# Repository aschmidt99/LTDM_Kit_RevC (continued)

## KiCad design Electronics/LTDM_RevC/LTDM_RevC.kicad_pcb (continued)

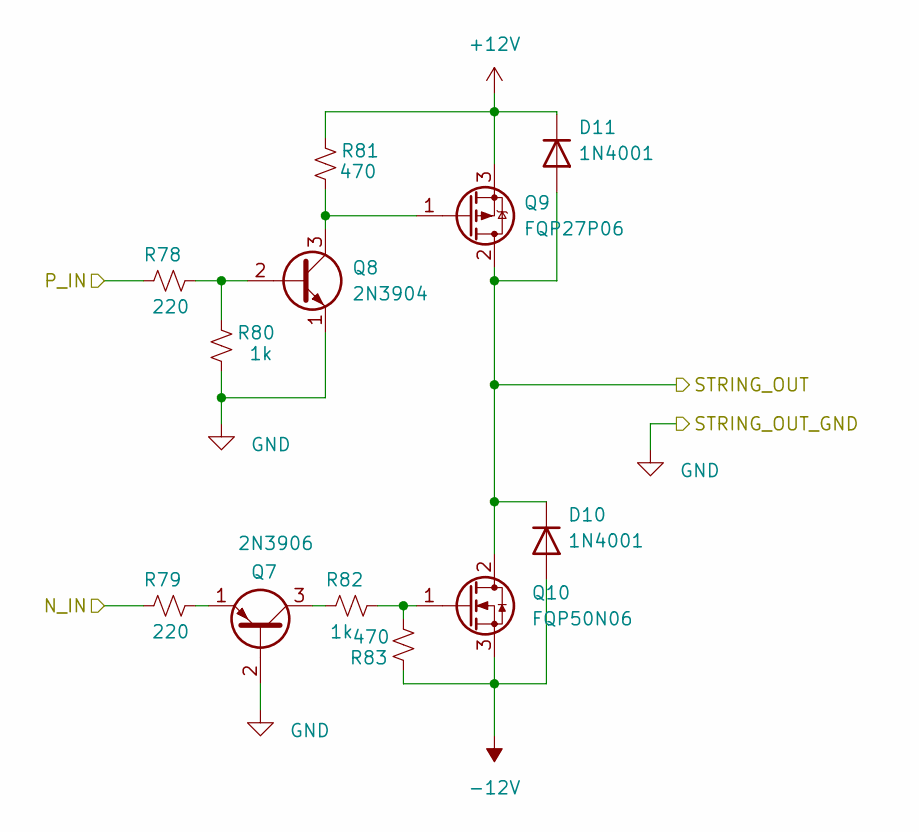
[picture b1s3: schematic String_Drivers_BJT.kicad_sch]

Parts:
D10, D11: 1N4001; D_DO-34_SOD68_P7.62mm_Horizontal
Q7: 2N3906; TO-92_Inline
Q8: 2N3904; TO-92_Inline
Q9: FQP27P06; TO-220-3_Vertical
Q10: FQP50N06; TO-220-3_Vertical; LCSC C2710
R78, R79: 220; R_0603_1608Metric
R80, R82: 1k; R_0603_1608Metric
R81, R83: 470; R_0603_1608Metric

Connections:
unnamed: D10.1 (K), D11.2 (A), Q9.2 (D), Q10.2 (D)
unnamed: D10.2 (A), Q10.3 (S), R83.2
unnamed: D11.1 (K), Q9.3 (S), R81.2
unnamed: Q7.1 (E), R79.2
unnamed: Q7.2 (B), Q8.1 (E), R80.1
unnamed: Q7.3 (C), R82.1
unnamed: Q8.2 (B), R78.2, R80.2
unnamed: Q8.3 (C), Q9.1 (G), R81.1
unnamed: Q10.1 (G), R82.2, R83.1

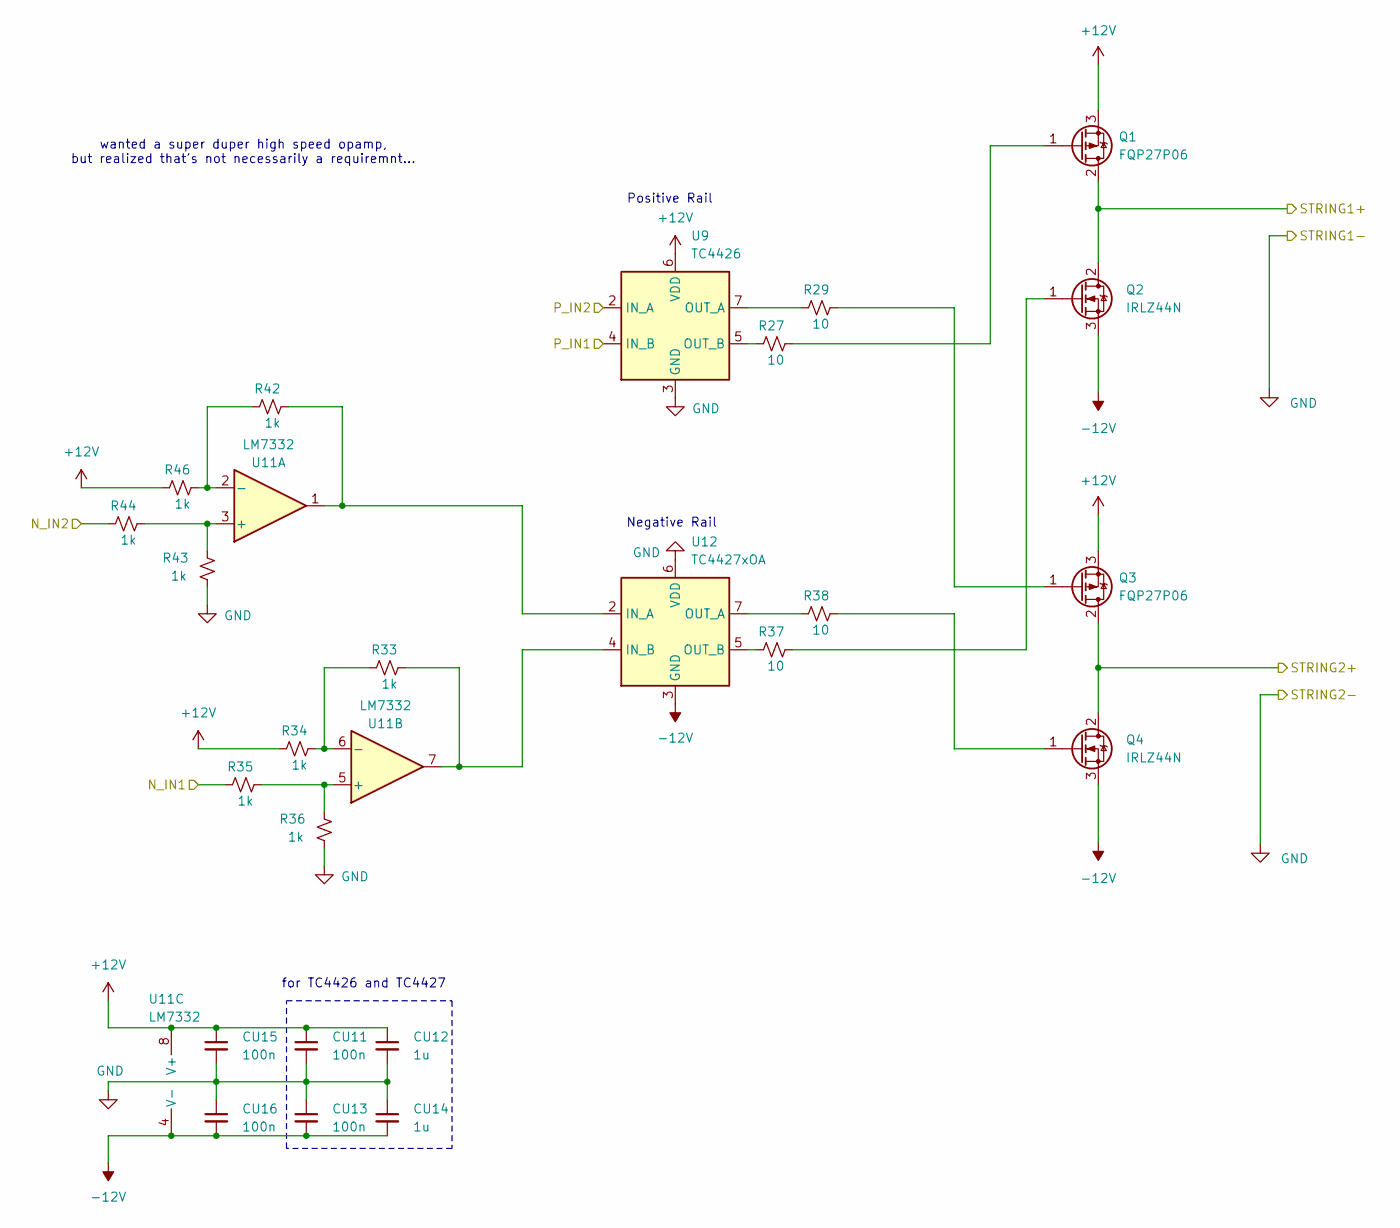
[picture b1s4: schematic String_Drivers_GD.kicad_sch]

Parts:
CU11, CU13, CU15, CU16: 100n; C_0603_1608Metric
CU12, CU14: 1u; C_0805_2012Metric; LCSC C24123
Q1, Q3: FQP27P06; TO-220-3_Vertical; LCSC C7503194
Q2, Q4: IRLZ44N; TO-220-3_Vertical; LCSC C22367197
R27, R29, R37, R38: 10; R_0603_1608Metric
R33, R34, R35, R36, R42, R43, R44, R46: 1k; R_0603_1608Metric
U9: TC4426; SOIC-8_3.9x4.9mm_P1.27mm; LCSC C148047
U11: LM7332; SOP-8_3.76x4.96mm_P1.27mm; LCSC C97826
U12: TC4427xOA; SOIC-8_3.9x4.9mm_P1.27mm; LCSC C636893

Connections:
+12V: CU11.1, CU12.1, CU15.1, Q1.3 (S), Q3.3 (S), R34.1, R46.1, U9.6 (VDD), U11.8 (V+); also elsewhere on the board
-12V: CU13.2, CU14.2, CU16.2, Q2.3 (S), Q4.3 (S), U11.4 (V-), U12.3 (GND); also elsewhere on the board
/String_Drivers_GD1/N_IN1: R35.1; also elsewhere on the board
/String_Drivers_GD1/N_IN2: R44.1; also elsewhere on the board
/String_Drivers_GD1/P_IN1: U9.4 (IN_B); also elsewhere on the board
/String_Drivers_GD1/P_IN2: U9.2 (IN_A); also elsewhere on the board
GND: CU11.2, CU12.2, CU13.1, CU14.1, CU15.2, CU16.1, R36.1, R43.1, U9.3 (GND), U12.6 (VDD); also elsewhere on the board
unnamed: Q1.1 (G), R27.2
unnamed: Q2.1 (G), R37.2
unnamed: Q3.1 (G), R29.2
unnamed: Q4.1 (G), R38.2
unnamed: R29.1, U9.7 (OUT_A)
unnamed: R27.1, U9.5 (OUT_B)
unnamed: R43.2, R44.2, U11.3 (+)
unnamed: R42.1, R46.2, U11.2 (-)
unnamed: R35.2, R36.2, U11.5 (+)
unnamed: R33.1, R34.2, U11.6 (-)
unnamed: R42.2, U11.1, U12.2 (IN_A)
unnamed: R33.2, U11.7, U12.4 (IN_B)
unnamed: R38.1, U12.7 (OUT_A)
unnamed: R37.1, U12.5 (OUT_B)
pre_resistor1: Q1.2 (D), Q2.2 (D); also elsewhere on the board
pre_resistor2: Q3.2 (D), Q4.2 (D); also elsewhere on the board

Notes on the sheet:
wanted a super duper high speed opamp, but realized that's not necessarily a requiremnt...
Negative Rail
Positive Rail
for TC4426 and TC4427

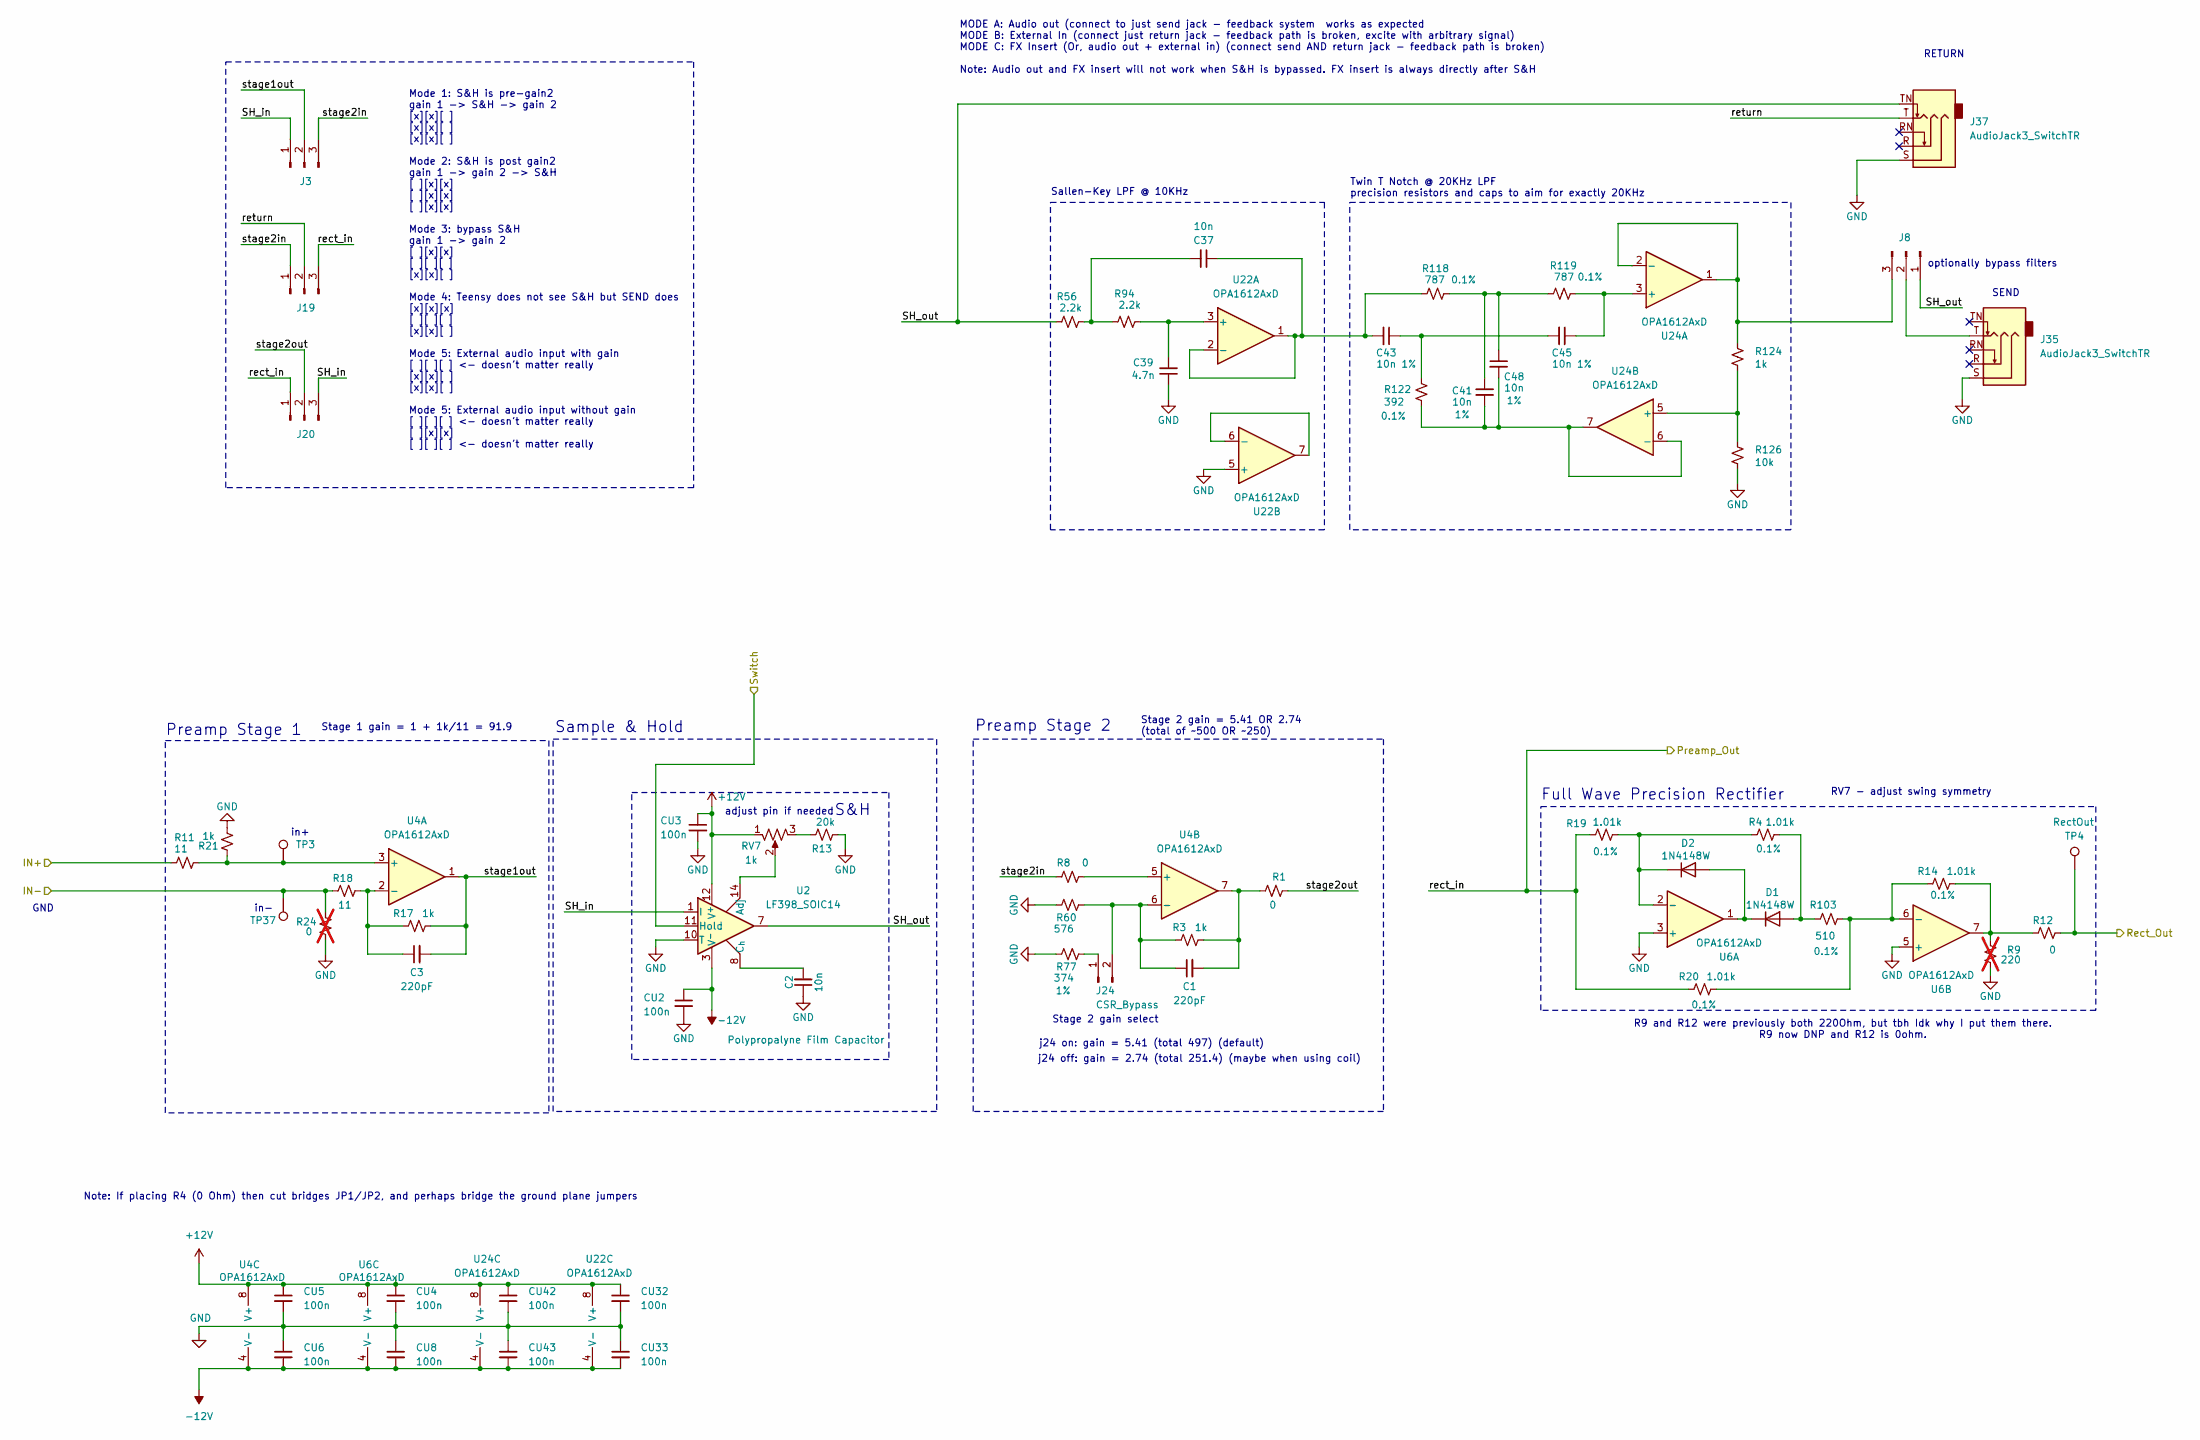
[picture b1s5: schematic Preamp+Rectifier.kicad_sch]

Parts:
C1, C3: 220pF; C_0603_1608Metric
C2: 10n; C_Rect_L11.0mm_W5.1mm_P10.00mm_MKT; LCSC C183540
C37: 10n; C_0603_1608Metric
C39: 4.7n; C_0603_1608Metric
C41, C43, C45, C48: 10n; C_0603_1608Metric; LCSC C3836718
CU2, CU3, CU4, CU5, CU6, CU8, CU32, CU33, CU42, CU43: 100n; C_0603_1608Metric
D1, D2: 1N4148W; D_SOD-123; LCSC C5345962
J3, J8, J19, J20: Conn_01x03_Male; PinHeader_1x03_P2.54mm_Vertical; LCSC C2914353
J24: CSR_Bypass; PinHeader_1x02_P2.54mm_Vertical; LCSC C124375
J35, J37: AudioJack3_SwitchTR; Jack_3.5mm_CUI_SJ1-3535NG_Horizontal; LCSC C4991610
R1, R8, R12: 0; R_0603_1608Metric
R3, R17, R21, R124: 1k; R_0603_1608Metric
R4, R14, R19, R20: 1.01k; R_0603_1608Metric; LCSC C861188
R9: 220; R_0603_1608Metric; not fitted
R11, R18: 11; R_0603_1608Metric; LCSC C861645
R13: 20k; R_0603_1608Metric
R24: 0; R_0603_1608Metric; not fitted
R56, R94: 2.2k; R_0603_1608Metric
R60: 576; R_0603_1608Metric; LCSC C705869
R77: 374; R_0603_1608Metric; LCSC C666871
R103: 510; R_0603_1608Metric; LCSC C309660
R118, R119: 787; R_0402_1005Metric; LCSC C728564
R122: 392; R_0603_1608Metric; LCSC C861870
R126: 10k; R_0603_1608Metric
RV7: 1k; Potentiometer_Bourns_3314G_Vertical; LCSC C780221
TP3, TP37: TestPoint; TestPoint_THTPad_D2.0mm_Drill1.0mm
TP4: RectOut; TestPoint_THTPad_D2.0mm_Drill1.0mm; LCSC C238122
U2: LF398_SOIC14; SOIC-14_3.9x8.7mm_P1.27mm; LCSC C2864267
U4, U6, U22, U24: OPA1612AxD; SOP-8_3.76x4.96mm_P1.27mm; LCSC C94590

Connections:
+12V: CU3.1, CU4.1, CU5.1, CU32.1, CU42.1, RV7.1, U2.12 (V^{+}), U4.8 (V+), U6.8 (V+), U22.8 (V+), U24.8 (V+); also elsewhere on the board
-12V: CU2.1, CU6.2, CU8.2, CU33.2, CU43.2, U2.3 (V^{-}), U4.4 (V-), U6.4 (V-), U22.4 (V-), U24.4 (V-); also elsewhere on the board
/Preamp+Rectifier1/IN+: R11.2; also elsewhere on the board
/Preamp+Rectifier1/IN-: R18.1, R24.2, TP37.1 (1_1); also elsewhere on the board
/Preamp+Rectifier1/Rect_Out: R12.2, TP4.1 (1_1); also elsewhere on the board
/Preamp+Rectifier1/SH_in: J3.1, J20.3, U2.1 (I)
/Preamp+Rectifier1/SH_out: J8.1, J37.TN, R56.2, U2.7
/Preamp+Rectifier1/rect_in: J19.3, J20.1, R19.1, R20.1; also elsewhere on the board
/Preamp+Rectifier1/return: J19.2, J37.T
/Preamp+Rectifier1/stage1out: C3.2, J3.2, R17.2, U4.1
/Preamp+Rectifier1/stage2in: J3.3, J19.1, R8.2
/Preamp+Rectifier1/stage2out: J20.2, R1.2
GND: C2.1, C39.1, CU2.2, CU3.2, CU4.2, CU5.2, CU6.1, CU8.1, CU32.2, CU33.1, CU42.2, CU43.1, J35.S, J37.S, R9.1, R13.2, R21.1, R24.1, R60.1, R77.1, R126.2, U2.10 (T), U6.3 (+), U6.5 (+), U22.5 (+); also elsewhere on the board
unnamed: C1.2, R1.1, R3.2, U4.7
unnamed: C37.2, R56.1, R94.2
unnamed: C41.1, C48.1, R118.1, R119.2
unnamed: C43.1, C45.2, R122.1
unnamed: D1.2 (A), R4.2, R103.1
unnamed: D1.1 (K), D2.2 (A), U6.1
unnamed: D2.1 (K), R4.1, R19.2, U6.2 (-)
unnamed: J8.2, J35.T
unnamed: J8.3, R124.1, U24.1, U24.2 (-)
unnamed: J24.1, R77.2
unnamed: C1.1, J24.2, R3.1, R60.2, U4.6 (-)
unnamed: R9.2, R12.1, R14.2, U6.7
unnamed: R13.1, RV7.3
unnamed: RV7.2, U2.14 (Adj)
unnamed: C2.2, U2.8 (C_{h})
unnamed: R11.1, R21.2, TP3.1 (1_1), U4.3 (+)
unnamed: C3.1, R17.1, R18.2, U4.2 (-)
unnamed: R8.1, U4.5 (+)
unnamed: R14.1, R20.2, R103.2, U6.6 (-)
unnamed: C39.2, R94.1, U22.3 (+)
unnamed: C37.1, C43.2, R118.2, U22.1, U22.2 (-)
unnamed: U22.6 (-), U22.7
unnamed: C45.1, R119.1, U24.3 (+)
unnamed: R124.2, R126.1, U24.5 (+)
unnamed: C41.2, C48.2, R122.2, U24.6 (-), U24.7
sample: U2.11 (Hold); also elsewhere on the board

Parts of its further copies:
C30, C34: 220pF; C_0603_1608Metric
C33: 10n; C_Rect_L11.0mm_W5.1mm_P10.00mm_MKT; LCSC C183540
C38: 10n; C_0603_1608Metric
C40: 4.7n; C_0603_1608Metric
C42, C44, C46, C49: 10n; C_0603_1608Metric; LCSC C3836718
CU18, CU19, CU21, CU23, CU24, CU25, CU39, CU40, CU44, CU45: 100n; C_0603_1608Metric
D7, D9: 1N4148W; D_SOD-123; LCSC C5345962
J10, J21, J27, J30: Conn_01x03_Male; PinHeader_1x03_P2.54mm_Vertical; LCSC C2914353
J28: CSR_Bypass; PinHeader_1x02_P2.54mm_Vertical; LCSC C124375
J36, J38: AudioJack3_SwitchTR; Jack_3.5mm_CUI_SJ1-3535NG_Horizontal; LCSC C4991610
R49, R59, R63: 0; R_0603_1608Metric
R51, R70, R73, R125: 1k; R_0603_1608Metric
R52, R65, R68, R69: 1.01k; R_0603_1608Metric; LCSC C861188
R57: 220; R_0603_1608Metric; not fitted
R58, R71: 11; R_0603_1608Metric; LCSC C861645
R62: 20k; R_0603_1608Metric
R64: 374; R_0603_1608Metric; LCSC C666871
R72, R117: 2.2k; R_0603_1608Metric
R75: 0; R_0603_1608Metric; not fitted
R76: 576; R_0603_1608Metric; LCSC C705869
R104: 510; R_0603_1608Metric; LCSC C309660
R120, R121: 787; R_0402_1005Metric; LCSC C728564
R123: 392; R_0603_1608Metric; LCSC C861870
R127: 10k; R_0603_1608Metric
RV10: 1k; Potentiometer_Bourns_3314G_Vertical; LCSC C780221
TP24: RectOut; TestPoint_THTPad_D2.0mm_Drill1.0mm; LCSC C238122
TP25, TP38: TestPoint; TestPoint_THTPad_D2.0mm_Drill1.0mm
U13, U14, U23, U25: OPA1612AxD; SOP-8_3.76x4.96mm_P1.27mm; LCSC C94590
U16: LF398_SOIC14; SOIC-14_3.9x8.7mm_P1.27mm; LCSC C2864267

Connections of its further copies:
+12V: CU18.1, CU19.1, CU23.1, CU39.1, CU44.1, RV10.1, U13.8 (V+), U14.8 (V+), U16.12 (V^{+}), U23.8 (V+), U25.8 (V+); also elsewhere on the board
-12V: CU21.2, CU24.1, CU25.2, CU40.2, CU45.2, U13.4 (V-), U14.4 (V-), U16.3 (V^{-}), U23.4 (V-), U25.4 (V-); also elsewhere on the board
/Preamp+Rectifier2/IN+: R58.2; also elsewhere on the board
/Preamp+Rectifier2/IN-: R71.1, R75.2, TP38.1 (1_1); also elsewhere on the board
/Preamp+Rectifier2/Rect_Out: R63.2, TP24.1 (1_1); also elsewhere on the board
/Preamp+Rectifier2/SH_in: J21.1, J30.3, U16.1 (I)
/Preamp+Rectifier2/SH_out: J10.1, J38.TN, R72.2, U16.7
/Preamp+Rectifier2/rect_in: J27.3, J30.1, R68.1, R69.1; also elsewhere on the board
/Preamp+Rectifier2/return: J27.2, J38.T
/Preamp+Rectifier2/stage1out: C34.2, J21.2, R70.2, U13.1
/Preamp+Rectifier2/stage2in: J21.3, J27.1, R59.2
/Preamp+Rectifier2/stage2out: J30.2, R49.2
GND: C33.1, C40.1, CU18.2, CU19.2, CU21.1, CU23.2, CU24.2, CU25.1, CU39.2, CU40.1, CU44.2, CU45.1, J36.S, J38.S, R57.1, R62.2, R64.1, R73.1, R75.1, R76.1, R127.2, U14.3 (+), U14.5 (+), U16.10 (T), U23.5 (+); also elsewhere on the board
unnamed: C30.2, R49.1, R51.2, U13.7
unnamed: C38.2, R72.1, R117.2
unnamed: C42.1, C49.1, R120.1, R121.2
unnamed: C44.1, C46.2, R123.1
unnamed: D7.2 (A), R52.2, R104.1
unnamed: D7.1 (K), D9.2 (A), U14.1
unnamed: D9.1 (K), R52.1, R68.2, U14.2 (-)
unnamed: J10.2, J36.T
unnamed: J10.3, R125.1, U25.1, U25.2 (-)
unnamed: J28.1, R64.2
unnamed: C30.1, J28.2, R51.1, R76.2, U13.6 (-)
unnamed: R57.2, R63.1, R65.2, U14.7
unnamed: R62.1, RV10.3
unnamed: R58.1, R73.2, TP25.1 (1_1), U13.3 (+)
unnamed: C34.1, R70.1, R71.2, U13.2 (-)
unnamed: R59.1, U13.5 (+)
unnamed: R65.1, R69.2, R104.2, U14.6 (-)
unnamed: RV10.2, U16.14 (Adj)
unnamed: C33.2, U16.8 (C_{h})
unnamed: C40.2, R117.1, U23.3 (+)
unnamed: C38.1, C44.2, R120.2, U23.1, U23.2 (-)
unnamed: U23.6 (-), U23.7
unnamed: C46.1, R121.1, U25.3 (+)
unnamed: R125.2, R127.1, U25.5 (+)
unnamed: C42.2, C49.2, R123.2, U25.6 (-), U25.7
sample: U16.11 (Hold); also elsewhere on the board

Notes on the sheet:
j24 off: gain = 2.74 (total 251.4) (maybe when using coil)
adjust pin if needed
optionally bypass filters
GND
S&H
SEND
Preamp Stage 1
Note: If placing R4 (0 Ohm) then cut bridges JP1/JP2, and perhaps bridge the ground plane jumpers
Sallen-Key LPF @ 10KHz
Sample & Hold
in-
Full Wave Precision Rectifier
Stage 2 gain select
in+
RETURN
Mode 1: S&H is pre-gain2 gain 1 -> S&H -> gain 2 [x][x][ ] [x][x][ ] [x][x][ ] Mode 2: S&H is post gain2 gain 1 -> gain 2 -> S&H [ ][x][x] [ ][x][x] [ ][x][x] Mode 3: bypass S&H gain 1 -> gain 2 [ ][x][x] [ ][ ][ ] [x][x][ ] Mode 4: Teensy does not see S&H but SEND does [x][x][x] [ ][ ][ ] [x][x][ 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
MODE A: Audio out (connect to just send jack - feedback system works as expected MODE B: External In (connect just return jack - feedback path is broken, excite with arbitrary signal) MODE C: FX Insert (Or, audio out + external in) (connect send AND return jack - feedback path is broken) Note: Audi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
RV7 - adjust swing symmetry
R9 and R12 were previously both 220Ohm, but tbh Idk why I put them there. R9 now DNP and R12 is 0ohm.
Stage 1 gain = 1 + 1k/11 = 91.9
Preamp Stage 2
j24 on: gain = 5.41 (total 497) (default)
Stage 2 gain = 5.41 OR 2.74 (total of ~500 OR ~250)
Twin T Notch @ 20KHz LPF precision resistors and caps to aim for exactly 20KHz

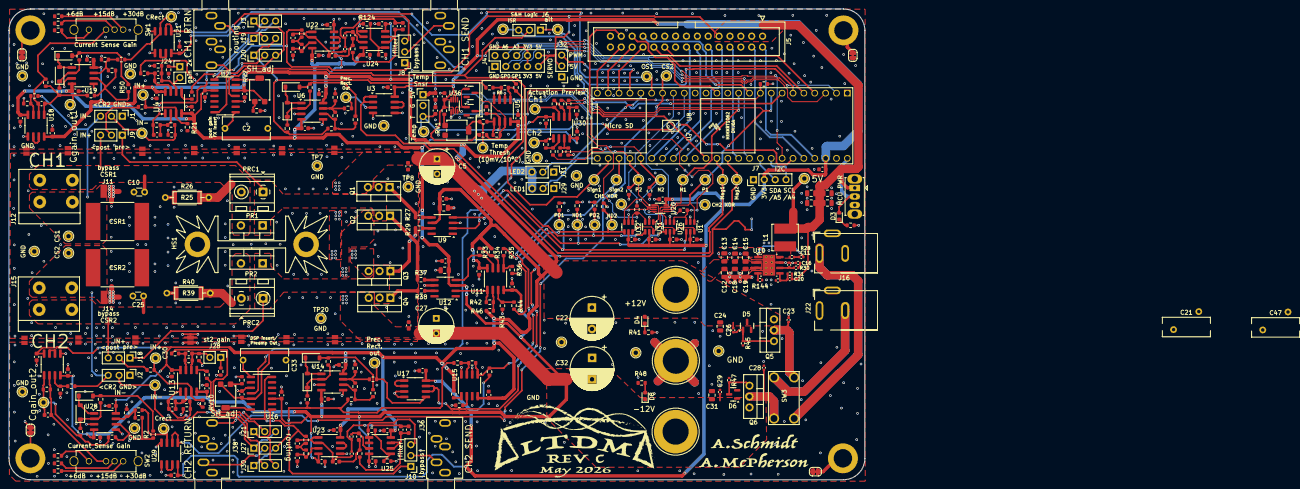
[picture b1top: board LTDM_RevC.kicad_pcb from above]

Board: 4 copper layers, 200.0 x 110.0 mm, 409 parts (1 on the bottom side), 206 nets.

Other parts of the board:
C21, C47: C_Small_US; C_Rect_L11.0mm_W4.3mm_P10.00mm_MKT

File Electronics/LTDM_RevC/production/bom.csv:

Designator,Footprint,Quantity,Value,LCSC Part #
"C1, C3, C30, C34, C35, C36",0603,6,220pF,
C11,0402,1,100n,
"C12, C13, C14, C15, C18, C19",0805,6,10u,C469541
C16,0402,1,1.2n,
"C2, C33",C_Rect_L11.0mm_W5.1mm_P10.00mm_MKT,2,10n,C183540
"C22, C32",CP_Radial_D10.0mm_P5.00mm,2,1000u,C2960265
"C23, C28",0402,2,100n,C162179
"C24, C31",0805,2,10u 35v,C469541
"C26, C29",0402,2,100n,C92753
"C27, C5",CP_Radial_D8.0mm_P3.50mm,2,220u,C45072
"C37, C38",0603,2,10n,
"C39, C40",0603,2,4.7n,
C4,CP_EIA-7343-31_Kemet-D,1,100u,C189619
"C41, C42, C43, C44, C45, C46, C48, C49",0603,8,10n,C3836718
"C6, C7, C8, C9",0805,4,10u,C117956
"CSR1, CSR2",R_4527,2,0.1R 5W,C5127890
"CU1, CU10, CU11, CU13, CU15, CU16, CU17, CU18, CU19, CU2, CU20, CU21, CU22, CU23, CU24, CU25, CU26, CU27, CU28, CU29, CU3, CU30, CU31, CU32, CU33, CU34, CU35, CU36, CU37, CU38, CU39, CU4, CU40, CU41, CU42, CU43, CU44, CU45, CU46, CU47, CU48, CU49, CU5, CU50, CU51, CU52, CU53, CU6, CU7, CU8, CU9",0603,51,100n,
"CU12, CU14",0805,2,1u,C24123
"D1, D14, D15, D16, D17, D2, D7, D9",D_SOD-123,8,1N4148W,C5345962
"D3, D4, D8",0603,3,LED,C79636
"D5, D6",SOT-23,2,MMBZ5242BLT3G,C896784
"J1, J10, J18, J19, J2, J20, J21, J23, J27, J29, J3, J30, J31, J32, J6, J8, J9",PinHeader_1x03_P2.54mm_Vertical,17,Conn_01x03_Male, C2914353
"J11, J14",SolderJumper-2_P1.3mm_Open_Pad1.0x1.5mm,2,CSR_Bypass,C124375
"J12, J15",TerminalBlock_Spring_2_P5.08mm,2,SpringTerminal,C35616
"J16, J22",BarrelJack_Wuerth_6941xx301002,2,Barrel_Jack,C3096082
"J24, J28",PinHeader_1x02_P2.54mm_Vertical,2,CSR_Bypass,C124375
"J35, J36, J37, J38",Jack_3.5mm_CUI_SJ1-3535NG_Horizontal,4,AudioJack3_SwitchTR,C4991610
J4,PinHeader_2x05_P2.54mm_Vertical,1,Conn_02x05_Odd_Even,C376087
J5,IDC-Header_2x15_P2.54mm_Vertical,1,Conn_02x15_Odd_Even,C358748
"JP1, JP2, JP20, JP21",SolderJumper-2_P1.3mm_Bridged_RoundedPad1.0x1.5mm,4,bridge,
"JP10, JP12, JP13, JP14, JP15, JP16, JP17, JP18, JP3, JP4, JP5, JP6, JP7, JP9",SolderJumper-2_subtle,14,GND,
L1,L_Bourns_SRN6045TA,1,3.3u,C3221229
"PRC1, PRC2",TerminalBlock_RND_205-00232_1x02_P5.08mm_Horizontal,2,Conn_01x02, C430601
PWR_SW1,SW_Slide_1P2T_CK_OS102011MS2Q,1,SW_SPST,C431547
"Q1, Q3, Q5",TO-220-3_Vertical,3,FQP27P06,C7503194
"Q15, Q16",SOT-23,2,BSS123,C78962
"Q2, Q4, Q6",TO-220-3_Vertical,3,IRLZ44N,C22367197
"R1, R115, R116, R12, R49, R59, R63, R8",0603,8,0,
"R10, R126, R127, R128, R129, R130, R131, R132, R133, R134, R135, R142, R143, R16, R22, R55, R61, R66, R74",0603,19,10k,
"R100, R124, R125, R137, R139, R15, R17, R21, R3, R33, R34, R35, R36, R42, R43, R44, R46, R5, R51, R53, R67, R70, R73, R92, R93, R95, R96, R97",0603,28,1k,
"R101, R98",0603,2,205,C403059
"R102, R99",0603,2,32.4,C861326
"R103, R104, R2, R41, R48, R50",0603,6,510,C309660
"R105, R106, R107, R108, R109, R110, R111, R112, R14, R19, R20, R4, R52, R65, R68, R69",0603,16,1.01k,C861188
"R11, R18, R58, R71",0603,4,11,C861645
"R117, R136, R56, R72, R94",0603,5,2.2k,
"R118, R119, R120, R121",0402,4,787,C728564
"R122, R123",0603,2,392,C861870
"R13, R62",0603,2,20k,
"R138, R54, R6",0603,3,1Meg,
"R140, R141",0603,2,4.7k,
R144,0402,1,176K,C862921
R23,0603,1,120,
"R26, R40",2512,2,100R 1W,C24920
"R27, R29, R37, R38",0603,4,10,
R28,0402,1,10R,C138066
R30,0402,1,20K,
R31,0402,1,12K,C25752
R32,0402,1,2.2k,
"R45, R47",0402,2,12K 1%,C25535
"R60, R76",0603,2,576,C705869
"R64, R77",0603,2,374,C666871
R7,0603,1,100k,
"R90, R91",0603,2,47,
"RV1, RV10, RV7",Potentiometer_Bourns_3314G_Vertical,3,1k,C780221
"SW1, SW2",SW_Slide-SSSS918700,2,SW_SP3T,C390919
SW3,PinHeader_2x02_P2.54mm_Vertical,1,SW_DPST, C5272597
"TP1, TP2",TestPoint_THTPad_D2.0mm_Drill1.0mm,2,TP,
"TP10, TP11, TP12, TP13, TP14, TP15, TP16, TP17, TP19, TP21, TP39, TP40, TP41, TP42, TP43, TP44, TP45, TP46, TP47, TP48, TP6, TP9",TestPoint_THTPad_D2.0mm_Drill1.0mm,22,TestPoint,C238122
"TP18, TP20, TP22, TP23, TP26, TP27, TP28, TP29, TP30, TP49, TP5, TP7, TP8",TestPoint_THTPad_D2.0mm_Drill1.0mm,13,TestPoint,C238127
"TP24, TP4",TestPoint_THTPad_D2.0mm_Drill1.0mm,2,RectOut,C238122
"TP25, TP3, TP37, TP38",TestPoint_THTPad_D2.0mm_Drill1.0mm,4,TestPoint,
"TP31, TP32",TestPoint_THTPad_D2.0mm_Drill1.0mm,2,CGain_Out2,C238122
"TP33, TP34",TestPoint_THTPad_D2.0mm_Drill1.0mm,2,CRect_Out1,C238122
"TP35, TP36",TestPoint_THTPad_D2.0mm_Drill1.0mm,2,CClamp_Out1,C238122
"U1, U26, U31, U32",SOT-23-6,4,74LVC1G11, C22356918
U10,SOIC-8-1EP_3.9x4.9mm_P1.27mm_EP2.95x4.9mm_Mask2.71x3.4mm_ThermalVias,1,AP64500SP,C2070920
U11,SOP-8_3.76x4.96mm_P1.27mm,1,LM7332,C97826
U12,SOIC-8_3.9x4.9mm_P1.27mm,1,TC4427xOA,C636893
"U13, U14, U18, U19, U22, U23, U24, U25, U27, U28, U30, U4, U6",SOP-8_3.76x4.96mm_P1.27mm,13,OPA1612AxD,C94590
"U15, U5",SOP-8_3.76x4.96mm_P1.27mm,2,LM393,C7955
"U16, U2",SOIC-14_3.9x8.7mm_P1.27mm,2,LF398_SOIC14,C2864267
"U17, U21, U29, U3",SOP-8_3.76x4.96mm_P1.27mm,4,OPA2350,C55904
U20,VSSOP-8_2.3x2mm_P0.5mm,1,74AUC2G86,C2876515
U36,VSSOP-8_2.3x2mm_P0.5mm,1,74LVC2G74,C7851
U7,Teensy4.1A,1,Teensy4.1A,C41376163
U8,Teensy4.1B,1,Teensy4.1B,C41376163
U9,SOIC-8_3.9x4.9mm_P1.27mm,1,TC4426,C148047

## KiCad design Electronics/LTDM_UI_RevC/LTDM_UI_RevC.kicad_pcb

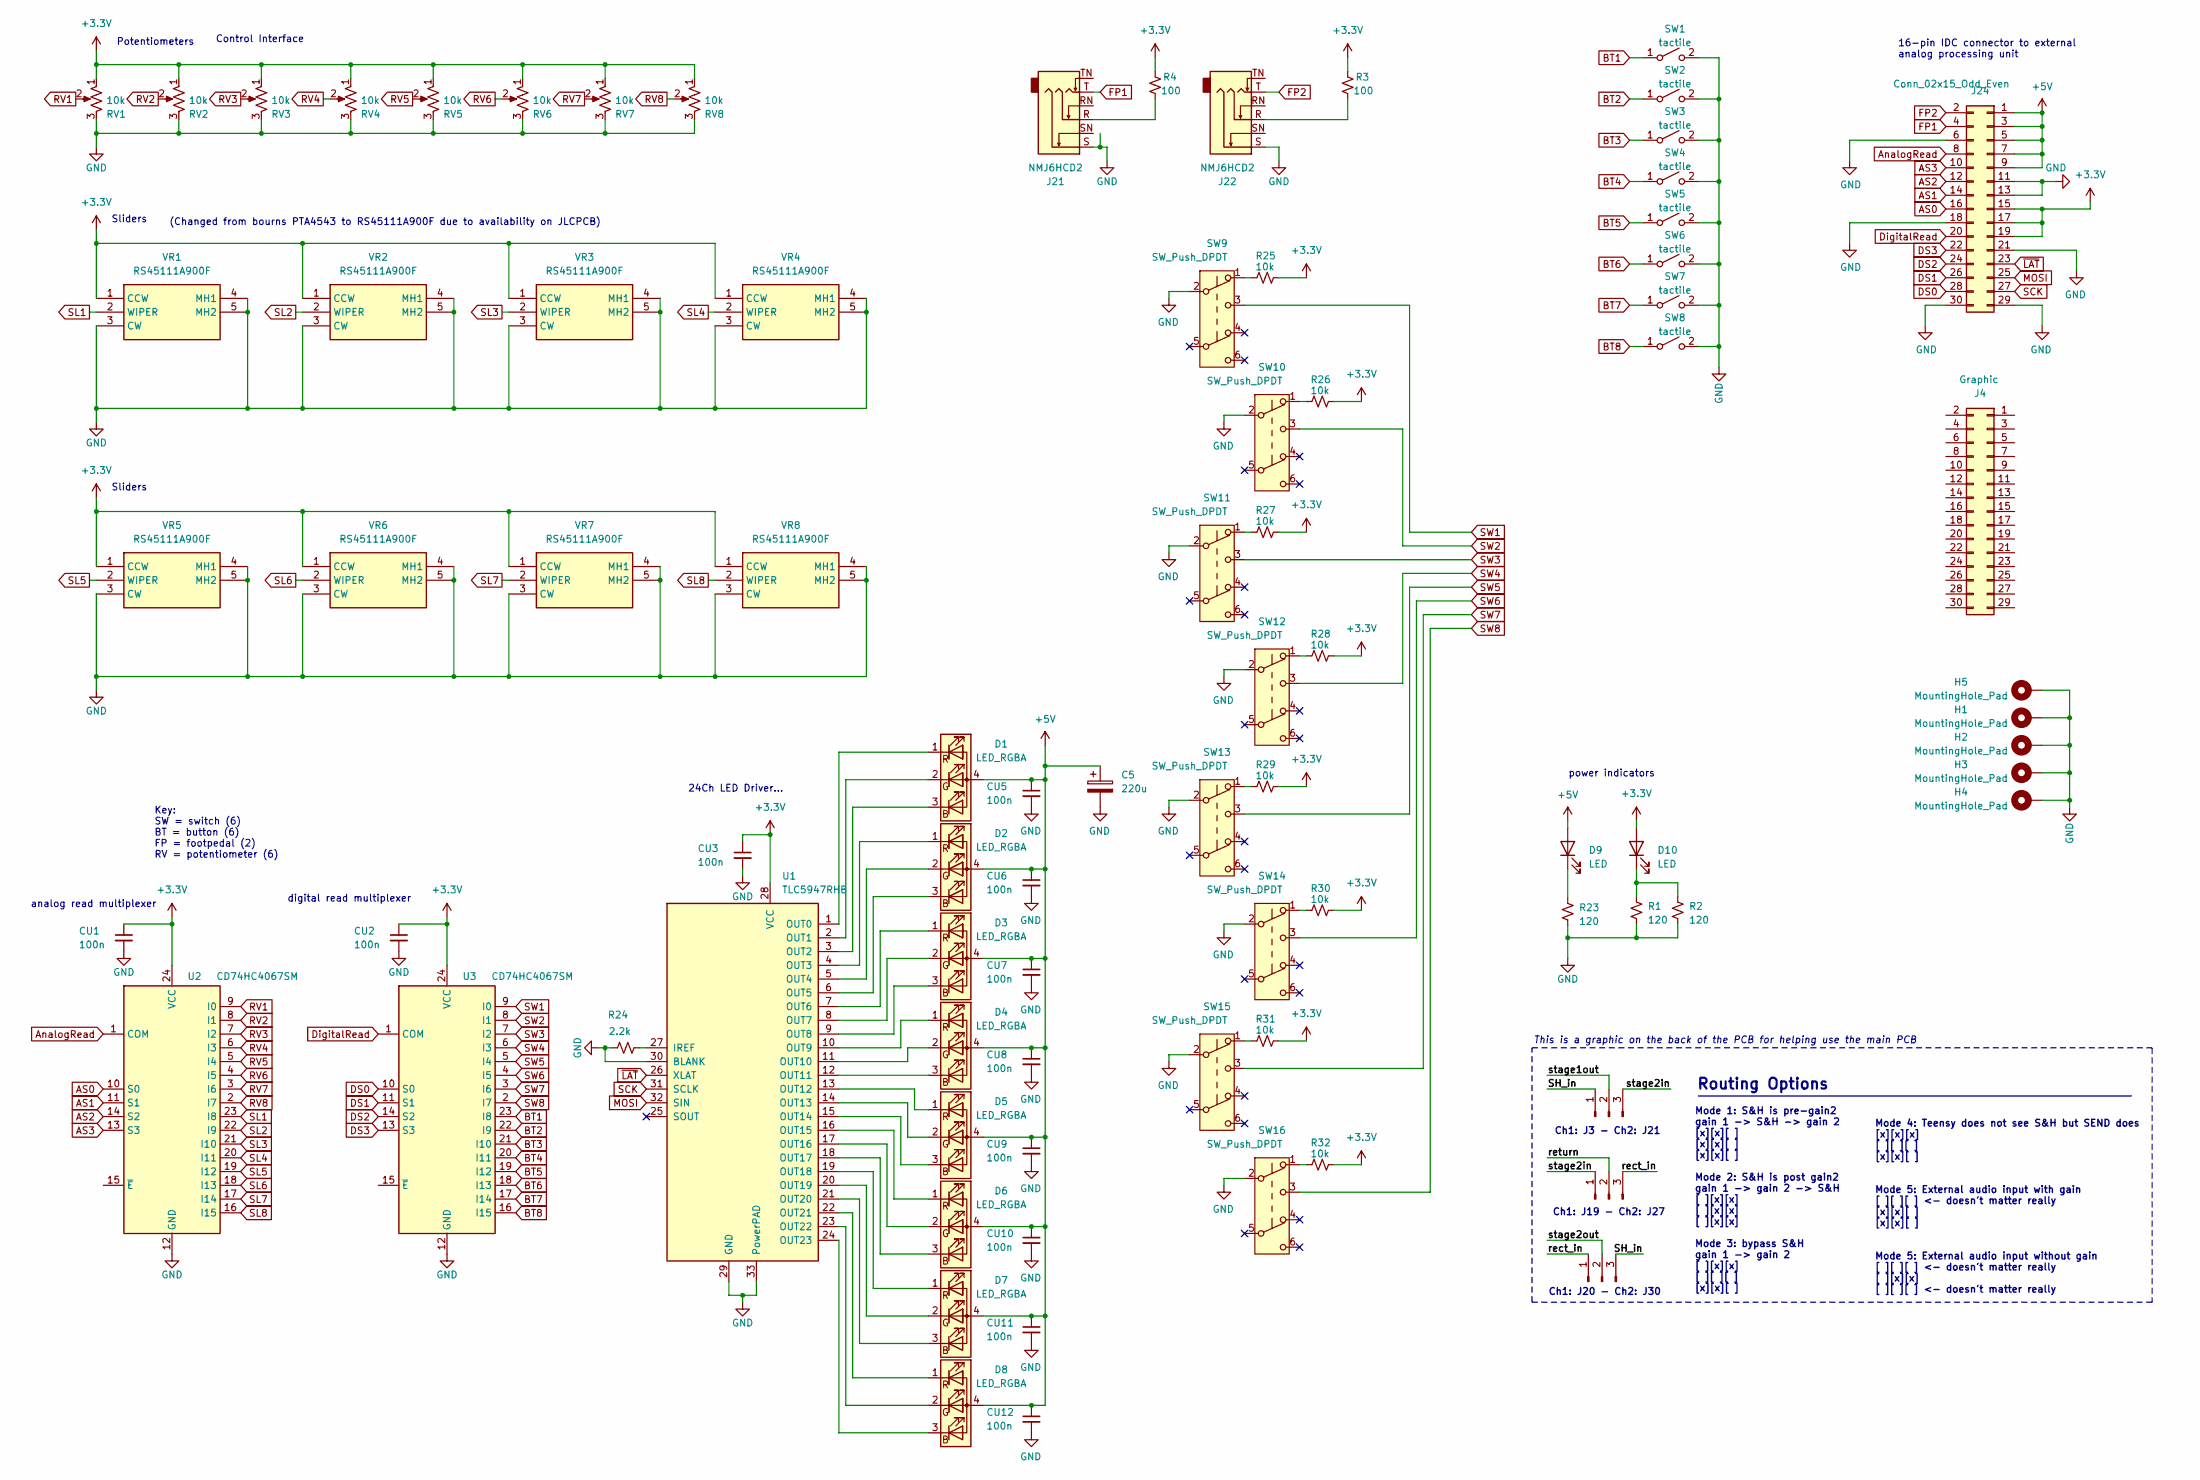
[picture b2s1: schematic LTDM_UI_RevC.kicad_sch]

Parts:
C5: 220u; CP_Radial_D8.0mm_P3.50mm; LCSC C45072
CU1, CU2, CU3, CU5, CU6, CU7, CU8, CU9, CU10, CU11, CU12: 100n; C_0603_1608Metric
D1, D2, D3, D4, D5, D6, D7, D8: LED_RGBA; 19237R6GHBHCA012T; LCSC C60105
D9, D10: LED; LED_0603_1608Metric; LCSC C79636
H1, H2, H3, H4, H5: MountingHole_Pad; MountingHole_4.3mm_M4_ISO14580_Pad
J1, J2, J3: Conn_01x03_Male
J4: Graphic; IDC-Header_2x15_P2.54mm_Vertical_SILKSCREEN; LCSC C358748
J21, J22: NMJ6HCD2; Jack_6.35mm_Neutrik_NMJ6HCD2_Horizontal; LCSC C368502
J24: Conn_02x15_Odd_Even; IDC-Header_2x15_P2.54mm_Vertical; LCSC C358748
R1, R2, R23: 120; R_0603_1608Metric
R3, R4: 100; R_0603_1608Metric
R24: 2.2k; R_0603_1608Metric
R25, R26, R27, R28, R29, R30, R31, R32: 10k; R_0603_1608Metric
RV1, RV2, RV3, RV4, RV5, RV6, RV7, RV8: 10k; Potentiometer_Bourns_PTV09A-1_Single_Vertical; LCSC C5357831
SW1, SW2, SW3, SW4, SW5, SW6, SW7, SW8: tactile; SW_Push_1P1T_NO_Vertical_Wuerth_434133025816; LCSC C5504987
SW9, SW10, SW11, SW12, SW13, SW14, SW15, SW16: SW_Push_DPDT; SW_Push_DPDT_PS-5850SVB-6PL; LCSC C5155567
U1: TLC5947RHB; QFN-32-1EP_5x5mm_P0.5mm_EP3.45x3.45mm; LCSC C181402
U2, U3: CD74HC4067SM; SSOP-24_5.3x8.2mm_P0.65mm; LCSC C98457
VR1, VR2, VR3, VR4, VR5, VR6, VR7, VR8: RS45111A900F; Mouser Part Number 688-RS45111A900F

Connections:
+3.3V: CU1.1, CU2.1, CU3.1, D10.2 (A), J24.15, J24.17, J24.19, R3.1, R4.1, R25.1, R26.1, R27.1, R28.1, R29.1, R30.1, R31.1, R32.1, RV1.1, RV2.1, RV3.1, RV4.1, RV5.1, RV6.1, RV7.1, RV8.1, U1.28 (VCC), U2.24 (VCC), U3.24 (VCC), VR1.1 (CCW), VR2.1 (CCW), VR3.1 (CCW), VR4.1 (CCW), VR5.1 (CCW), VR6.1 (CCW), VR7.1 (CCW), VR8.1 (CCW)
+5V: C5.1, CU5.1, CU6.1, CU7.1, CU8.1, CU9.1, CU10.1, CU11.1, CU12.1, D1.4 (A), D2.4 (A), D3.4 (A), D4.4 (A), D5.4 (A), D6.4 (A), D7.4 (A), D8.4 (A), D9.2 (A), J24.1, J24.3, J24.5, J24.7, J24.9
AS0: J24.16, U2.10 (S0)
AS1: J24.14, U2.11 (S1)
AS2: J24.12, U2.14 (S2)
AS3: J24.10, U2.13 (S3)
AnalogRead: J24.8, U2.1 (COM)
BT1: SW1.1 (A), U3.23 (I8)
BT2: SW2.1 (A), U3.22 (I9)
BT3: SW3.1 (A), U3.21 (I10)
BT4: SW4.1 (A), U3.20 (I11)
BT5: SW5.1 (A), U3.19 (I12)
BT6: SW6.1 (A), U3.18 (I13)
BT7: SW7.1 (A), U3.17 (I14)
BT8: SW8.1 (A), U3.16 (I15)
DS0: J24.28, U3.10 (S0)
DS1: J24.26, U3.11 (S1)
DS2: J24.24, U3.14 (S2)
DS3: J24.22, U3.13 (S3)
DigitalRead: J24.20, U3.1 (COM)
FP1: J21.T, J24.4
FP2: J22.T, J24.2
GND: C5.2, CU1.2, CU2.2, CU3.2, CU5.2, CU6.2, CU7.2, CU8.2, CU9.2, CU10.2, CU11.2, CU12.2, H1.1, H2.1, H3.1, H4.1, H5.1, J21.S, J22.S, J24.6, J24.11, J24.13, J24.18, J24.21, J24.29, J24.30, R1.1, R2.1, R23.1, R24.2, RV1.3, RV2.3, RV3.3, RV4.3, RV5.3, RV6.3, RV7.3, RV8.3, SW1.2 (B), SW2.2 (B), SW3.2 (B), SW4.2 (B), SW5.2 (B), SW6.2 (B), SW7.2 (B), SW8.2 (B), SW9.2 (B), SW10.2 (B), SW11.2 (B), SW12.2 (B), SW13.2 (B), SW14.2 (B), SW15.2 (B), SW16.2 (B), U1.29 (GND), U1.30 (BLANK), U1.33 (PowerPAD), U2.12 (GND), U3.12 (GND), VR1.3 (CW), VR1.4 (MH1), VR1.5 (MH2), VR2.3 (CW), VR2.4 (MH1), VR2.5 (MH2), VR3.3 (CW), VR3.4 (MH1), VR3.5 (MH2), VR4.3 (CW), VR4.4 (MH1), VR4.5 (MH2), VR5.3 (CW), VR5.4 (MH1), VR5.5 (MH2), VR6.3 (CW), VR6.4 (MH1), VR6.5 (MH2), VR7.3 (CW), VR7.4 (MH1), VR7.5 (MH2), VR8.3 (CW), VR8.4 (MH1), VR8.5 (MH2)
MOSI: J24.25, U1.32 (SIN)
unnamed: D1.3 (BK), U1.3 (OUT2)
unnamed: D1.2 (GK), U1.2 (OUT1)
unnamed: D1.1 (RK), U1.1 (OUT0)
unnamed: D2.3 (BK), U1.6 (OUT5)
unnamed: D2.2 (GK), U1.5 (OUT4)
unnamed: D2.1 (RK), U1.4 (OUT3)
unnamed: D3.3 (BK), U1.9 (OUT8)
unnamed: D3.2 (GK), U1.8 (OUT7)
unnamed: D3.1 (RK), U1.7 (OUT6)
unnamed: D4.3 (BK), U1.12 (OUT11)
unnamed: D4.2 (GK), U1.11 (OUT10)
unnamed: D4.1 (RK), U1.10 (OUT9)
unnamed: D5.3 (BK), U1.15 (OUT14)
unnamed: D5.2 (GK), U1.14 (OUT13)
unnamed: D5.1 (RK), U1.13 (OUT12)
unnamed: D6.3 (BK), U1.18 (OUT17)
unnamed: D6.2 (GK), U1.17 (OUT16)
unnamed: D6.1 (RK), U1.16 (OUT15)
unnamed: D7.3 (BK), U1.21 (OUT20)
unnamed: D7.2 (GK), U1.20 (OUT19)
unnamed: D7.1 (RK), U1.19 (OUT18)
unnamed: D8.3 (BK), U1.24 (OUT23)
unnamed: D8.2 (GK), U1.23 (OUT22)
unnamed: D8.1 (RK), U1.22 (OUT21)
unnamed: D9.1 (K), R23.2
unnamed: D10.1 (K), R1.2, R2.2
unnamed: J1.1, J3.3
unnamed: J1.3, J2.1
unnamed: J2.3, J3.1
unnamed: J21.R, R4.2
unnamed: J22.R, R3.2
unnamed: R25.2, SW9.1 (A)
unnamed: R26.2, SW10.1 (A)
unnamed: R27.2, SW11.1 (A)
unnamed: R28.2, SW12.1 (A)
unnamed: R29.2, SW13.1 (A)
unnamed: R30.2, SW14.1 (A)
unnamed: R31.2, SW15.1 (A)
unnamed: R32.2, SW16.1 (A)
unnamed: R24.1, U1.27 (IREF)
RV1: RV1.2, U2.9 (I0)
RV2: RV2.2, U2.8 (I1)
RV3: RV3.2, U2.7 (I2)
RV4: RV4.2, U2.6 (I3)
RV5: RV5.2, U2.5 (I4)
RV6: RV6.2, U2.4 (I5)
RV7: RV7.2, U2.3 (I6)
RV8: RV8.2, U2.2 (I7)
SCK: J24.27, U1.31 (SCLK)
SL1: U2.23 (I8), VR1.2 (WIPER)
SL2: U2.22 (I9), VR2.2 (WIPER)
SL3: U2.21 (I10), VR3.2 (WIPER)
SL4: U2.20 (I11), VR4.2 (WIPER)
SL5: U2.19 (I12), VR5.2 (WIPER)
SL6: U2.18 (I13), VR6.2 (WIPER)
SL7: U2.17 (I14), VR7.2 (WIPER)
SL8: U2.16 (I15), VR8.2 (WIPER)
SW1: SW9.3 (C), U3.9 (I0)
SW2: SW10.3 (C), U3.8 (I1)
SW3: SW11.3 (C), U3.7 (I2)
SW4: SW12.3 (C), U3.6 (I3)
SW5: SW13.3 (C), U3.5 (I4)
SW6: SW14.3 (C), U3.4 (I5)
SW7: SW15.3 (C), U3.3 (I6)
SW8: SW16.3 (C), U3.2 (I7)
~LAT: J24.23, U1.26 (XLAT)

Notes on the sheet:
(Changed from bourns PTA4543 to RS45111A900F due to availability on JLCPCB)
24Ch LED Driver...
Mode 4: Teensy does not see S&H but SEND does [x][x][x] [ ][ ][ ] [x][x][ ] Mode 5: External audio input with gain [ ][ ][ ] <- doesn't matter really [x][x][ ] [x][x][ ] Mode 5: External audio input without gain [ ][ ][ ] <- doesn't matter really [ ][x][x] [ ][ ][ ] <- doesn't matter really
Sliders
Control Interface
digital read multiplexer
This is a graphic on the back of the PCB for helping use the main PCB
Key: SW = switch (6) BT = button (6) FP = footpedal (2) RV = potentiometer (6)
Potentiometers
Routing Options
Mode 1: S&H is pre-gain2 gain 1 -> S&H -> gain 2 [x][x][ ] [x][x][ ] [x][x][ ] Mode 2: S&H is post gain2 gain 1 -> gain 2 -> S&H [ ][x][x] [ ][x][x] [ ][x][x] Mode 3: bypass S&H gain 1 -> gain 2 [ ][x][x] [ ][ ][ ] [x][x][ ]
Ch1: J3 - Ch2: J21
16-pin IDC connector to external analog processing unit
Ch1: J19 - Ch2: J27
power indicators
Ch1: J20 - Ch2: J30
analog read multiplexer
